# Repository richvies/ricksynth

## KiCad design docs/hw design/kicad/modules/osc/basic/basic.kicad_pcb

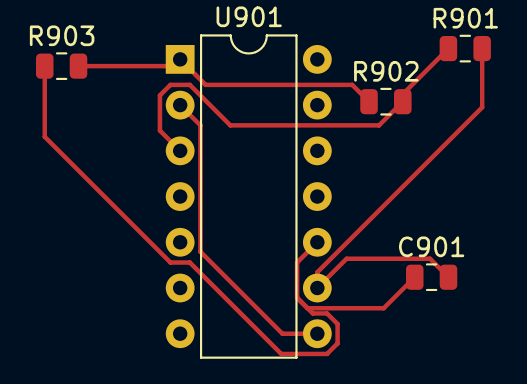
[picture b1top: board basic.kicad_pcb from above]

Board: 2 copper layers, 5 parts (0 on the bottom side), 5 nets.

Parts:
C901: 100n; C_0805_2012Metric
R901, R902, R903: 10k; R_0805_2012Metric
U901: LM324; DIP-14_W7.62mm

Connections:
/sq1: R902.1, R903.2, U901.1
/tri1: U901.2, U901.8
GND: C901.2, R901.2, U901.9
unnamed: C901.1, R903.1, U901.10
unnamed: R901.1, R902.2, U901.3

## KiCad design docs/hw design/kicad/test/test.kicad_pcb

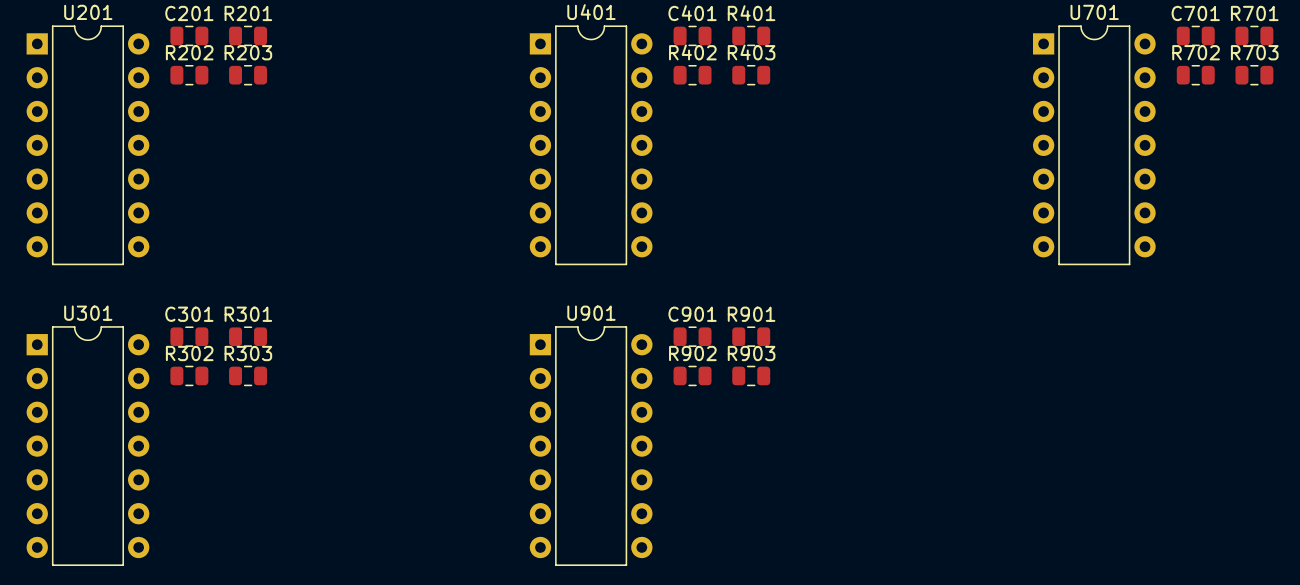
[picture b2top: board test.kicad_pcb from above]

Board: 2 copper layers, 25 parts (0 on the bottom side), 21 nets, no tracks yet.

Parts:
C201, C301, C401, C701, C901: 100n; C_0805_2012Metric
R201, R202, R203, R301, R302, R303, R401, R402, R403, R701, R702, R703, R901, R902, R903: 10k; R_0805_2012Metric
U201, U301, U401, U701, U901: LM324; DIP-14_W7.62mm

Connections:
/Sheet606A8BE8/Sheet606A8C08/Sheet606A8C26/sq1: R702.1, R703.2, U701.1
/Sheet606A8BE8/Sheet606A8C08/Sheet606A8C26/tri1: U701.2, U701.8
/Sheet606A95C9/Sheet606A95E2/sq1: R902.1, R903.2, U901.1
/Sheet606A95C9/Sheet606A95E2/tri1: U901.2, U901.8
/Sheet60689D46/sq1: R202.1, R203.2, U201.1
/Sheet60689D46/tri1: U201.2, U201.8
/sheet6068B9BE/sq1: R402.1, R403.2, U401.1
/sheet6068B9BE/tri1: U401.2, U401.8
/sheet60689DCE/sq1: R302.1, R303.2, U301.1
/sheet60689DCE/tri1: U301.2, U301.8
GND: C201.2, C301.2, C401.2, C701.2, C901.2, R201.2, R301.2, R401.2, R701.2, R901.2, U201.9, U301.9, U401.9, U701.9, U901.9
unnamed: C201.1, R203.1, U201.10
unnamed: C301.1, R303.1, U301.10
unnamed: C401.1, R403.1, U401.10
unnamed: C701.1, R703.1, U701.10
unnamed: C901.1, R903.1, U901.10
unnamed: R201.1, R202.2, U201.3
unnamed: R301.1, R302.2, U301.3
unnamed: R401.1, R402.2, U401.3
unnamed: R701.1, R702.2, U701.3
unnamed: R901.1, R902.2, U901.3

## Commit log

2021-07-17 + draw.io diagram
2021-07-17 Working build
2022-02-16 change dir structure
2022-02-19 intro work
2022-02-20 add mal
2022-03-06 makefile update
2022-03-07 dont track lib files
2022-04-10 start work on dio & i2c
2022-04-13 startup + cleanup files
2022-04-14 add clock startup config
2022-04-15 fix compiler warnings
2022-04-15 make mal separate library
2022-04-16 add delay fns
2022-04-18 add alarms + init 1ms system timer
2022-04-19 add custom bash history
2022-04-21 add dma support
2022-04-22 update bash profile
2022-04-22 update i2c interrupt handling & compiling for debug vs release
2022-04-22 prepare for c++
2022-04-22 add pcf8575 io expander
2022-04-23 update vscode config
2022-04-23 reorganize files + add mutex
2022-04-23 update pcf8578 & i2c to use callbacks
2022-04-25 fix pcf8575 init
2022-04-25 fix pcf compiling
2022-04-26 i2c + dma working
2022-04-29 PCF8575 update callback use
2022-04-29 add spi driver
2022-04-30 add board test files
2022-06-05 add adc, spi still not working
2022-08-19 fix spi array
2022-08-19 heavy changes to split mcu exported and private
2022-08-21 fix adc init
2022-08-21 remove mutex, dont call mcu fns from interrupts or callbacks
2022-08-22 i2c, irq: use ctxs to simplify irq handling
2022-08-29 i2c: fix read fn
2022-08-29 add doxygen
2022-08-29 spi: update to use irq contexts
2022-08-29 spi: update documentation
2022-08-30 bash profile: increase history size
2022-09-18 add cmsis dsp library
2022-09-18 include all hal modules
2022-10-21 heavy changes creating best board folder and making spi q work
2022-10-21 fix makefile and add w25qxx chip
2022-10-21 add link time optimization
2022-10-21 start w25q work
2022-10-25 add littlefs
2022-10-28 add first board test
2022-10-28 move littlefs to libs folder
2022-10-31 build working again after rearranging
2022-11-02 use void* for writing data to flash
2022-11-06 add test for builtin led on black pill board
2022-11-06 add stlink debug configuration
2022-11-06 change flashing option to stlink
2022-11-06 add notes.txt
2022-11-08 update spi to be even cleaner + update i2c
2022-11-08 add wm8731 start
2022-11-08 add cubemx config & report doc
2022-12-19 flash onboard led test working
2022-12-24 fix io config
2023-02-15 change how mcu & board config is done
2023-02-16 implement basic lfs storage
2023-02-16 continue cleanup of hw info
2023-02-16 remove uneeded includes from config
2023-02-16 add event for board processing
2023-04-08 change spi transport to allow start next xfer from interrupt. Not publicly tho
